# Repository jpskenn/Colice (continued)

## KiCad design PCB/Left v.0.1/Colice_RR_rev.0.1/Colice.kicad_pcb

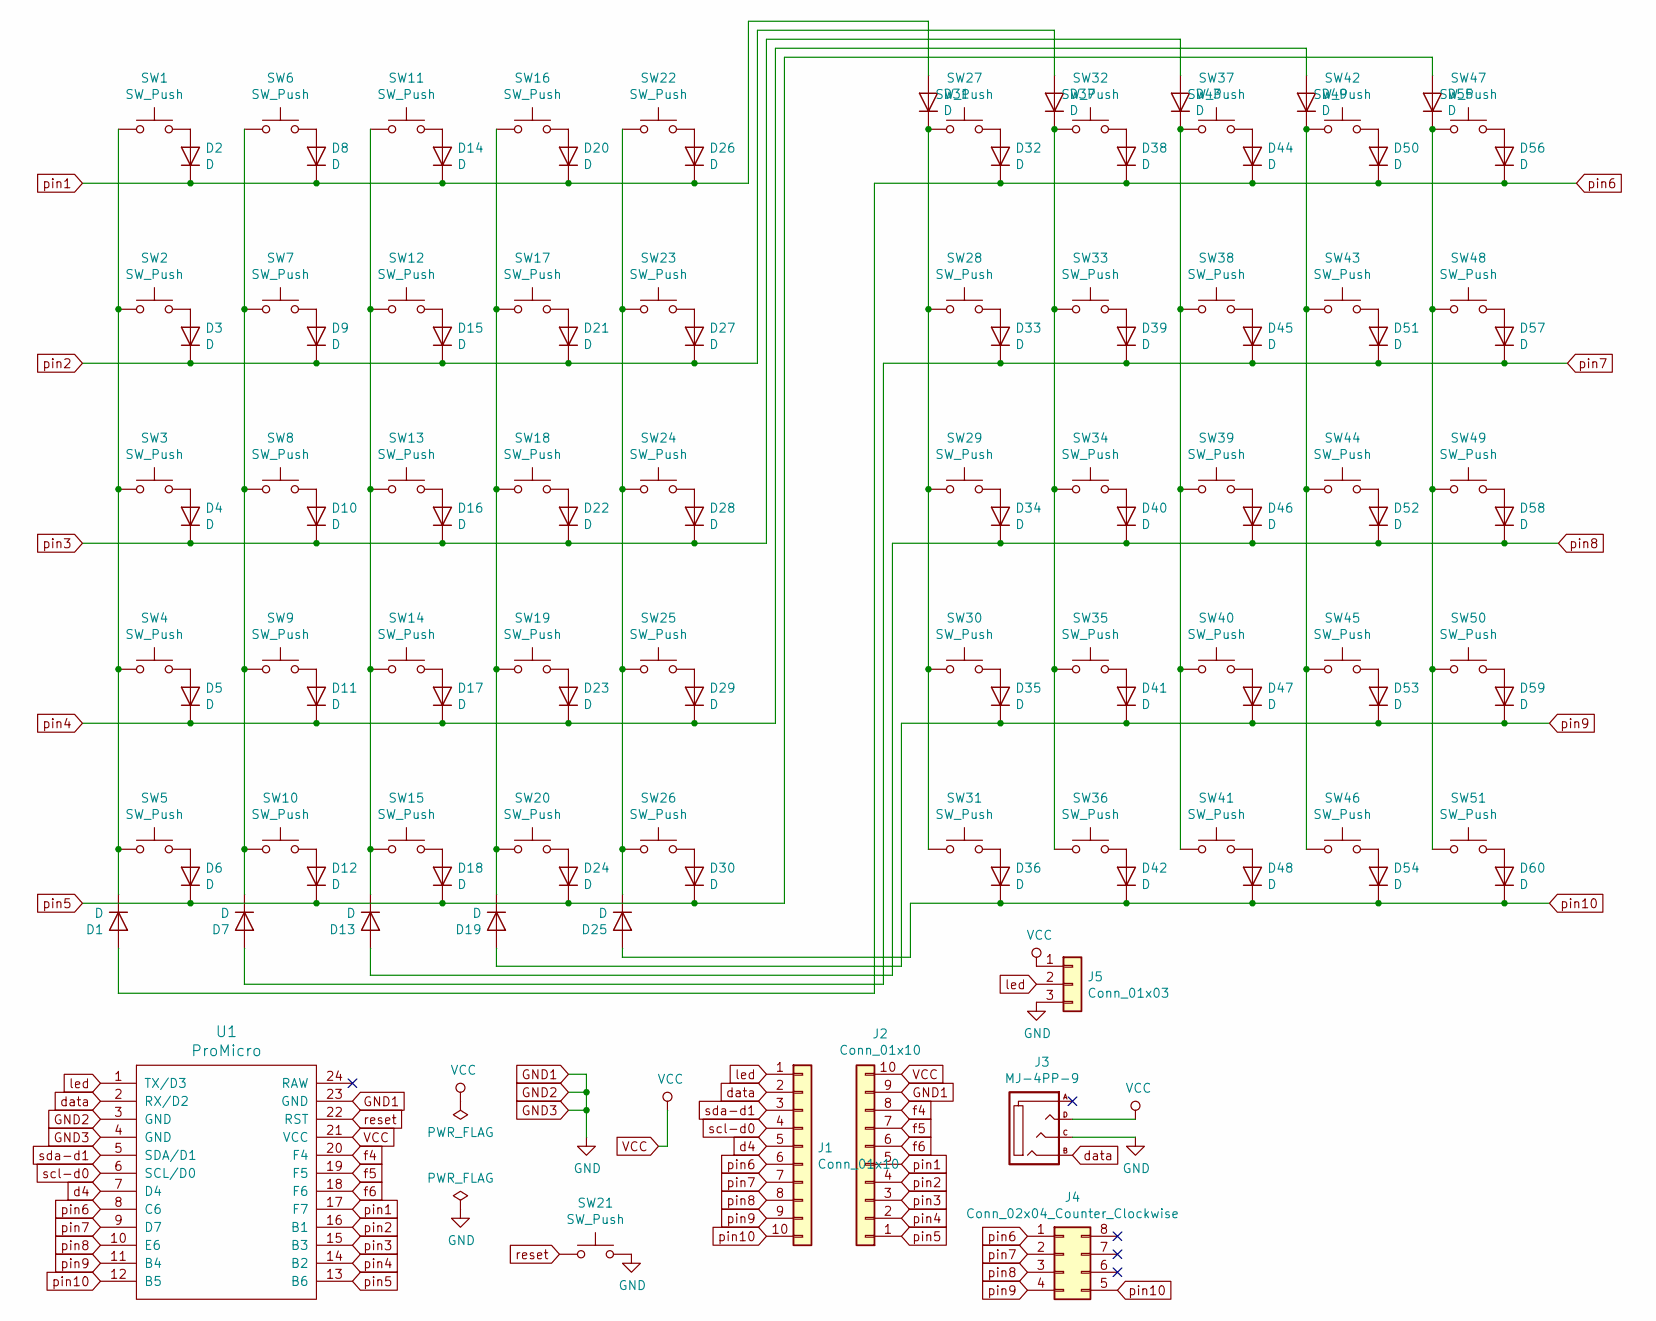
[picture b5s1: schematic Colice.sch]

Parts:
D1, D2, D3, D4, D5, D6, D7, D8, D9, D10, D11, D12, D13, D14, D15, D16, D17, D18, D19, D20, D21, D22, D23, D24, D25, D26, D27, D28, D29, D30, D31, D32, D33, D34, D35, D36, D37, D38, D39, D40, D41, D42, D43, D44, D45, D46, D47, D48, D49, D50, D51, D52, D53, D54, D55, D56, D57, D58, D59, D60: D; D3_TH_SMD
J1, J2: Conn_01x10; PinHeader_1x10_P2.54mm_Vertical
J3: MJ-4PP-9
J4: Conn_02x04_Counter_Clockwise; PinSocket_2x04_P2.54mm_Horizontal
J5: Conn_01x03; Pin_Header_Straight_1x03
SW1, SW2, SW3, SW4, SW5, SW6, SW7, SW8, SW9, SW10, SW11, SW12, SW13, SW14, SW15, SW16, SW17, SW18, SW19, SW20, SW22, SW23, SW24, SW25, SW26, SW27, SW28, SW29, SW30, SW31, SW32, SW33, SW34, SW35, SW36, SW37, SW38, SW39, SW40, SW41, SW42, SW43, SW44, SW45, SW46, SW47, SW48, SW49, SW50, SW51: SW_Push; CherryMX_Hotswap_v2
SW21: SW_Push; ResetSW
U1: ProMicro

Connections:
GND1: J2.9, J3.C, J5.3, SW21.2, U1.3 (GND), U1.4 (GND), U1.23 (GND)
unnamed: D1.1 (K), SW1.1, SW2.1, SW3.1, SW4.1, SW5.1
unnamed: D2.2 (A), SW1.2
unnamed: D3.2 (A), SW2.2
unnamed: D4.2 (A), SW3.2
unnamed: D5.2 (A), SW4.2
unnamed: D6.2 (A), SW5.2
unnamed: D7.1 (K), SW6.1, SW7.1, SW8.1, SW9.1, SW10.1
unnamed: D8.2 (A), SW6.2
unnamed: D9.2 (A), SW7.2
unnamed: D10.2 (A), SW8.2
unnamed: D11.2 (A), SW9.2
unnamed: D12.2 (A), SW10.2
unnamed: D13.1 (K), SW11.1, SW12.1, SW13.1, SW14.1, SW15.1
unnamed: D14.2 (A), SW11.2
unnamed: D15.2 (A), SW12.2
unnamed: D16.2 (A), SW13.2
unnamed: D17.2 (A), SW14.2
unnamed: D18.2 (A), SW15.2
unnamed: D19.1 (K), SW16.1, SW17.1, SW18.1, SW19.1, SW20.1
unnamed: D20.2 (A), SW16.2
unnamed: D21.2 (A), SW17.2
unnamed: D22.2 (A), SW18.2
unnamed: D23.2 (A), SW19.2
unnamed: D24.2 (A), SW20.2
unnamed: D25.1 (K), SW22.1, SW23.1, SW24.1, SW25.1, SW26.1
unnamed: D26.2 (A), SW22.2
unnamed: D27.2 (A), SW23.2
unnamed: D28.2 (A), SW24.2
unnamed: D29.2 (A), SW25.2
unnamed: D30.2 (A), SW26.2
unnamed: D31.1 (K), SW27.1, SW28.1, SW29.1, SW30.1, SW31.1
unnamed: D32.2 (A), SW27.2
unnamed: D33.2 (A), SW28.2
unnamed: D34.2 (A), SW29.2
unnamed: D35.2 (A), SW30.2
unnamed: D36.2 (A), SW31.2
unnamed: D37.1 (K), SW32.1, SW33.1, SW34.1, SW35.1, SW36.1
unnamed: D38.2 (A), SW32.2
unnamed: D39.2 (A), SW33.2
unnamed: D40.2 (A), SW34.2
unnamed: D41.2 (A), SW35.2
unnamed: D42.2 (A), SW36.2
unnamed: D43.1 (K), SW37.1, SW38.1, SW39.1, SW40.1, SW41.1
unnamed: D44.2 (A), SW37.2
unnamed: D45.2 (A), SW38.2
unnamed: D46.2 (A), SW39.2
unnamed: D47.2 (A), SW40.2
unnamed: D48.2 (A), SW41.2
unnamed: D49.1 (K), SW42.1, SW43.1, SW44.1, SW45.1, SW46.1
unnamed: D50.2 (A), SW42.2
unnamed: D51.2 (A), SW43.2
unnamed: D52.2 (A), SW44.2
unnamed: D53.2 (A), SW45.2
unnamed: D54.2 (A), SW46.2
unnamed: D55.1 (K), SW47.1, SW48.1, SW49.1, SW50.1, SW51.1
unnamed: D56.2 (A), SW47.2
unnamed: D57.2 (A), SW48.2
unnamed: D58.2 (A), SW49.2
unnamed: D59.2 (A), SW50.2
unnamed: D60.2 (A), SW51.2
VCC: J2.10, J3.D, J5.1, U1.21 (VCC)
d4: J1.5, U1.7 (D4)
data: J1.2, J3.B, U1.2 (RX/D2)
f4: J2.8, U1.20 (F4)
f5: J2.7, U1.19 (F5)
f6: J2.6, U1.18 (F6)
led: J1.1, J5.2, U1.1 (TX/D3)
pin1: D2.1 (K), D8.1 (K), D14.1 (K), D20.1 (K), D26.1 (K), D31.2 (A), J2.5, U1.17 (F7)
pin2: D3.1 (K), D9.1 (K), D15.1 (K), D21.1 (K), D27.1 (K), D37.2 (A), J2.4, U1.16 (B1)
pin3: D4.1 (K), D10.1 (K), D16.1 (K), D22.1 (K), D28.1 (K), D43.2 (A), J2.3, U1.15 (B3)
pin4: D5.1 (K), D11.1 (K), D17.1 (K), D23.1 (K), D29.1 (K), D49.2 (A), J2.2, U1.14 (B2)
pin5: D6.1 (K), D12.1 (K), D18.1 (K), D24.1 (K), D30.1 (K), D55.2 (A), J2.1, U1.13 (B6)
pin6: D1.2 (A), D32.1 (K), D38.1 (K), D44.1 (K), D50.1 (K), D56.1 (K), J1.6, J4.1, U1.8 (C6)
pin7: D7.2 (A), D33.1 (K), D39.1 (K), D45.1 (K), D51.1 (K), D57.1 (K), J1.7, J4.2, U1.9 (D7)
pin8: D13.2 (A), D34.1 (K), D40.1 (K), D46.1 (K), D52.1 (K), D58.1 (K), J1.8, J4.3, U1.10 (E6)
pin9: D19.2 (A), D35.1 (K), D41.1 (K), D47.1 (K), D53.1 (K), D59.1 (K), J1.9, J4.4, U1.11 (B4)
pin10: D25.2 (A), D36.1 (K), D42.1 (K), D48.1 (K), D54.1 (K), D60.1 (K), J1.10, J4.5, U1.12 (B5)
reset: SW21.1, U1.22 (RST)
scl-d0: J1.4, U1.6 (SCL/D0)
sda-d1: J1.3, U1.5 (SDA/D1)

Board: 2 copper layers, 117 parts (0 on the bottom side), 81 nets, no tracks yet.

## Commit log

2020-05-30 Add 写真素材追加
2020-05-30 Update 写真追加。特徴追記。
2020-05-30 Update 画像ファイル名変更
2025-01-15 ローカルデータをリポジトリへ配置
